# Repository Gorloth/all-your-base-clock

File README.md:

all-your-base-clock
===================

Project files for the All your base are belong to us clock

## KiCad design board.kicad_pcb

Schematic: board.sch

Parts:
C1: 10uF
C2, C3, C4, C5, C6: .1uF
P1, P2: CONN_8
R1: 150
RP1: R_PACK-47ohm
RP2: R_PACK4-47ohm
U1, U2: 74LS595
U3, U4: CD74ACT257M96; MODULE
U5: 74LVC1G14
U6: FDC6305N; MODULE
U7: RG7SEG; MODULE

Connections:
/Clk: P1.6, P2.6, U1.11 (SRCLK), U2.11 (SRCLK)
/Din: P1.7, U1.14 (SER), U2.14 (SER)
/Dout: P2.7, U1.9 (~QH)
/Glatch: P1.4, P2.4, U2.12 (RCLK)
/OE: P1.2, P2.2, U3.15 (OE), U4.15 (OE)
/R/G sel: P1.3, P2.3, U3.1 (S), U4.1 (S), U5.2, U6.1 (G1)
/Rlatch: P1.5, P2.5, U1.12 (RCLK)
GND: C1.2, C2.2, C3.2, C4.2, C5.2, C6.2, P1.1, P2.1, U1.8 (GND), U1.13 (G), U2.8 (GND), U2.13 (G), U3.8 (GND), U4.8 (GND), U5.3 (GND), U6.2 (S2), U6.5 (S1)
unnamed: U2.2 (QC), U4.6 (2B)
unnamed: U2.6 (QG), U3.10 (3B)
unnamed: U2.5 (QF), U3.13 (4B)
unnamed: U2.7 (QH), U4.3 (1B)
unnamed: U2.15 (QA), U3.6 (2B)
unnamed: U2.1 (QB), U3.3 (1B)
unnamed: U1.7 (QH), U4.2 (1A)
unnamed: U2.3 (QD), U4.10 (3B)
unnamed: U2.4 (QE), U4.13 (4B)
unnamed: U1.2 (QC), U4.5 (2A)
unnamed: U1.1 (QB), U3.2 (1A)
unnamed: U1.15 (QA), U3.5 (2A)
unnamed: U6.4 (D2), U7.5
unnamed: U1.4 (QE), U4.14 (4A)
unnamed: U1.6 (QG), U3.11 (3A)
unnamed: U1.5 (QF), U3.14 (4A)
unnamed: U1.3 (QD), U4.11 (3A)
unnamed: U5.4, U6.3 (G2)
unnamed: RP1.5 (R4), U7.4
unnamed: RP2.4, U7.6
unnamed: RP2.1, U7.10
unnamed: RP1.4, U4.7 (2O)
unnamed: U6.6 (D1), U7.1
unnamed: RP1.2, U4.9 (3O)
unnamed: RP1.7 (R2), U7.3
unnamed: RP2.8 (R1), U3.9 (3O)
unnamed: RP2.6 (R3), U3.7 (2O)
unnamed: RP2.5 (R4), U3.4 (1O)
unnamed: R1.1, U4.4 (1O)
unnamed: RP2.3, U7.7
unnamed: RP2.2, U7.9
unnamed: RP1.8 (R1), U7.2
unnamed: RP2.7 (R2), U3.12 (4O)
unnamed: R1.2, U7.8
unnamed: RP1.1, U4.12 (4O)
VCC: C1.1, C2.1, C3.1, C4.1, C5.1, C6.1, P1.8, P2.8, U1.10 (SRCLR), U1.16 (VCC), U2.10 (SRCLR), U2.16 (VCC), U3.16 (VCC), U4.16 (VCC), U5.5 (VCC)

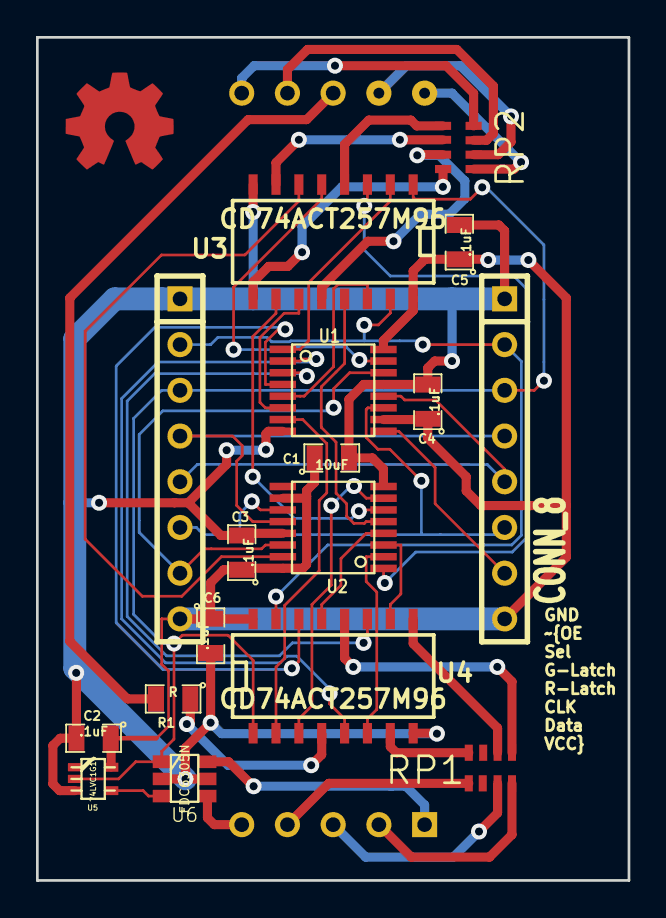
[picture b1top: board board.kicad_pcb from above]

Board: 2 copper layers, 32.9 x 46.8 mm, 18 parts (1 on the bottom side), 44 nets.

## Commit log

2014-05-29 Initial schematic
2014-06-09 Update schematic, initial board layout, add gerber files output for easier board creation
2015-05-05 Update board layout and gerber outputs
